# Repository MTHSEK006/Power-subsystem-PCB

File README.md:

**EEE3088 Power Sub-system Project 
MTHSEK006 & MKFMOR011**

**Description**  

This project involves the design and development of the micro-mouse power sub-system. The power sub-system is used to power the entire micro-mouse. This project is designed and developed in Kicad. Production files are jlcpcb compatible because project PCB is developed by JLCPCB. There are eight requirements in total. These requirements will be equally divided between MTHSEK006 and MFKMOR011. MTHSEK006 requirements designs can be found under pearl_pcb_design branch and MFKMOR011 requirements design can be found under morena_pcb_design branch. MTHSEK006 requirements include: 
* The power sub-system should operate 4 motors.
* The power sub-system should have a battery monitoring module.
* The power sub-system should provide 2x external load switching.
* The power sub-system should have a ON/OFF switch.
  
MFKMORO11 requirements include: 
* The power sub-system battery should be charged.
* The power sub-system should have two charging modes.
* The power sub-system should be integrated with a USB-C port.
* The power sub-system should have a 3V3 and 5V output channel.
At the end of the project, the power sub-system should be able to integrate with other components of the micro-mouse which include the motherboard, processor, sensing unit and the microcontroller.

**Structure**  

* PCB_v2.1: This includes the final PCB design. Contains Kicad files. 
* PCB_v2: This is the intial PCB design. Contains Kicad files.
* Documents: This includes footprints, symbol libraries, datasheets. 
* Production: Contains the gerber, clp and bom files.

**Usage**

  * The files needed to produce this PCB are found under Production. This folder can be downloaded and directly used for production.  
  * The final PCB design can be viewed by downloading PCB_v2.1 and opening the project in Kicad. 
 
**Contact** 

* Pearl Mothiba- MTHSEK006@myuct.ac.za
* Morena Mofokeng- MKFMOR011@myuct.ac.za
  
**Authors and Acknowledgement**

Authors 
* Pearl Mothiba
* Morena Mofokeng

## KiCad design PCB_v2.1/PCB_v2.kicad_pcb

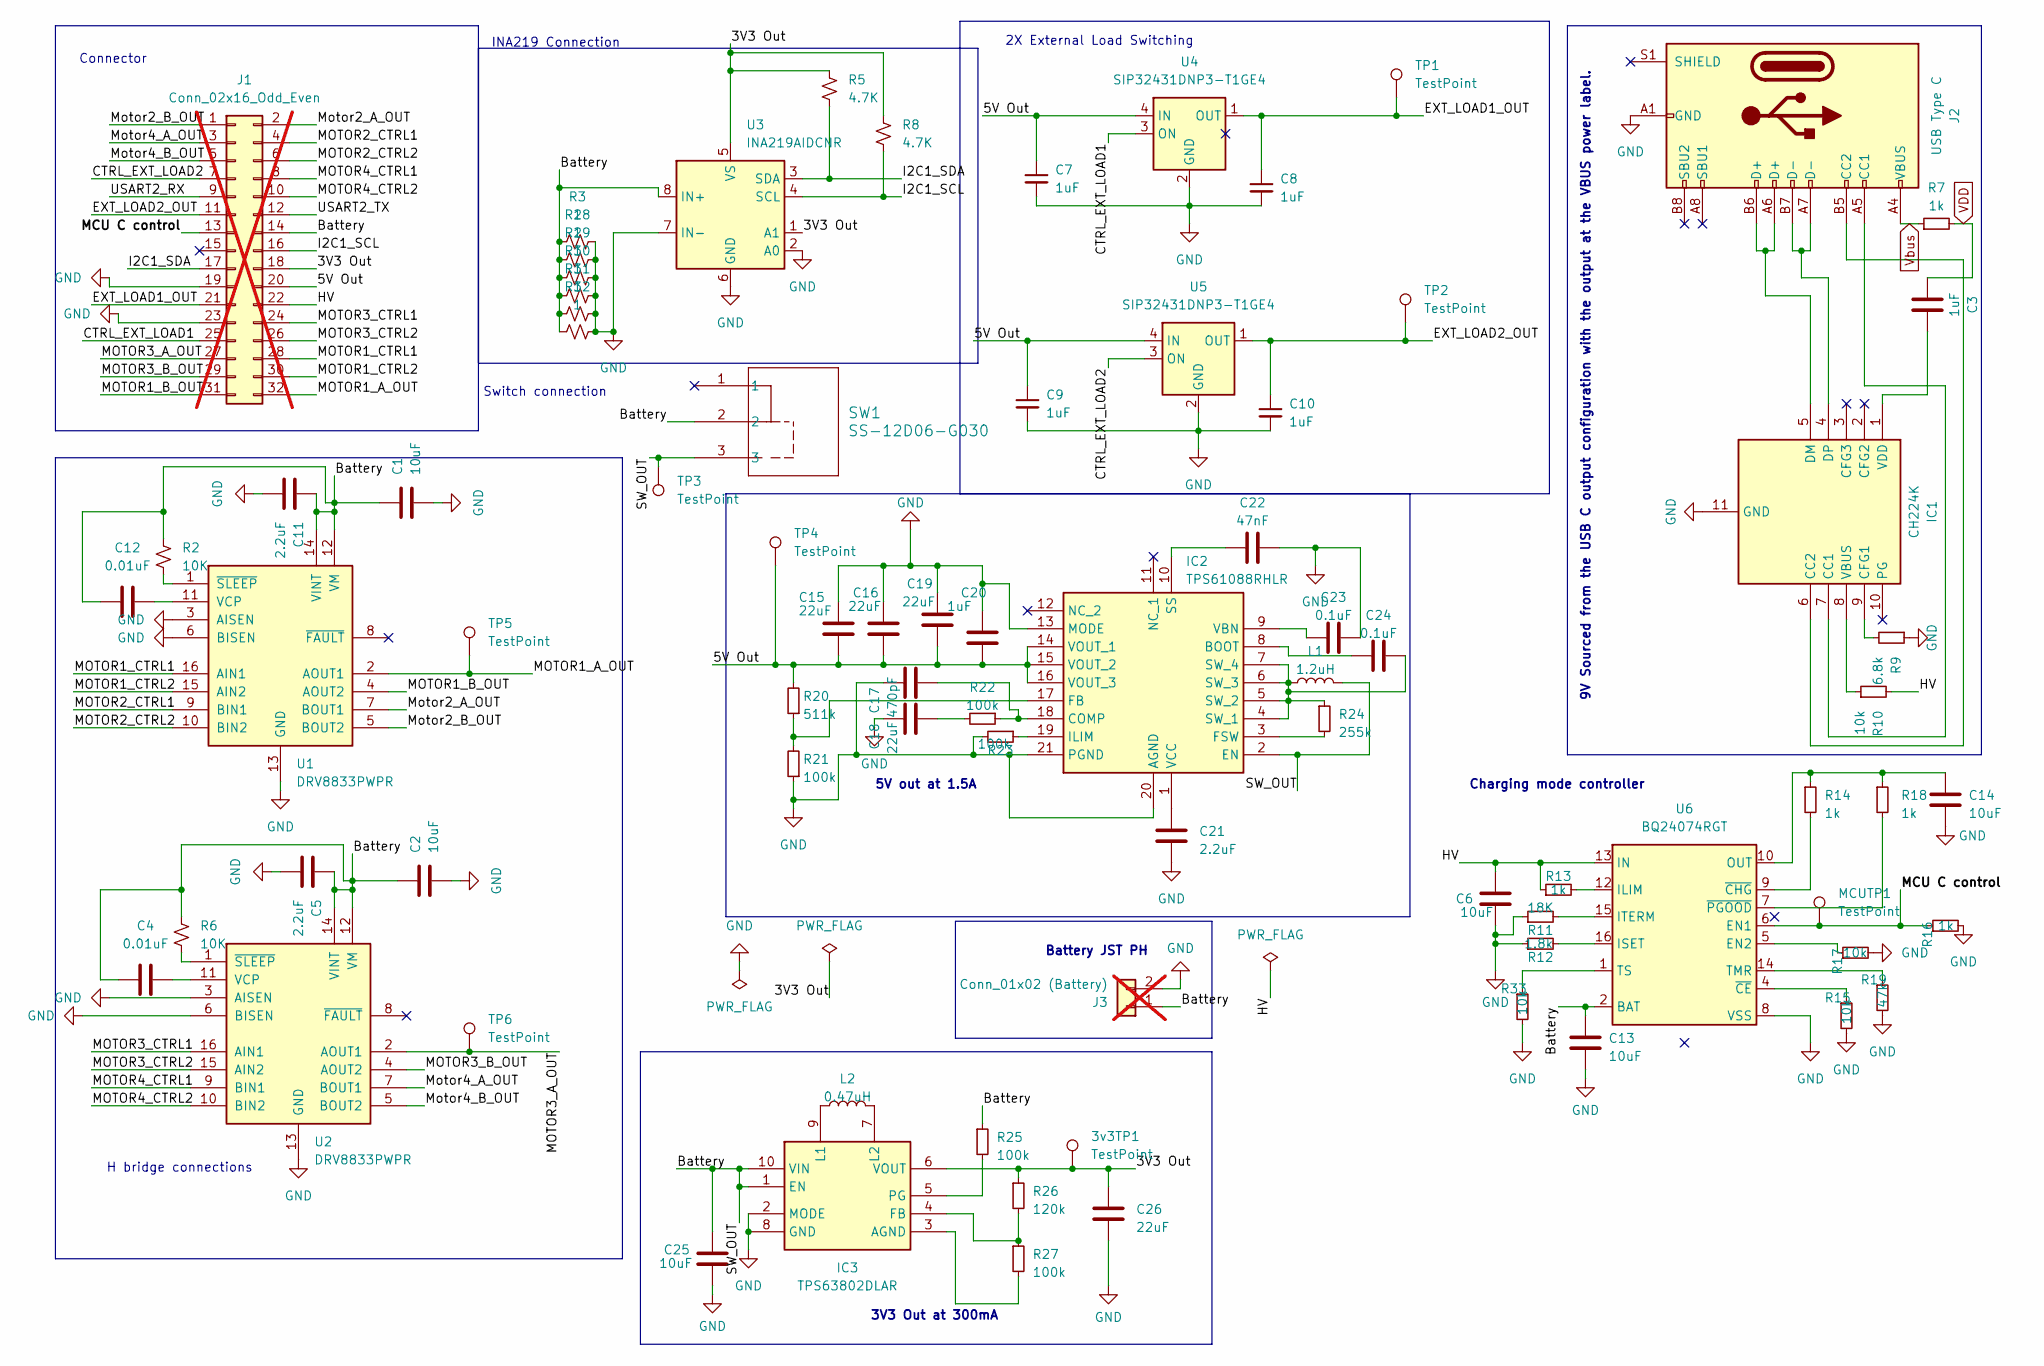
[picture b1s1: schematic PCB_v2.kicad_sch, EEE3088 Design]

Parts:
3v3TP1: TestPoint; TestPoint_Pad_1.0x1.0mm
C1, C2, C6, C13, C14, C25: 10uF; C_1206_3216Metric_Pad1.33x1.80mm_HandSolder; LCSC C13585
C3, C7, C8, C9, C10: 1uF; C_1206_3216Metric_Pad1.33x1.80mm_HandSolder; LCSC C1848
C4, C12: 0.01uF; C_0805_2012Metric_Pad1.18x1.45mm_HandSolder; LCSC C1710
C5, C11, C21: 2.2uF; C_0603_1608Metric_Pad1.08x0.95mm_HandSolder; LCSC C23630
C15, C16, C18, C19, C26: 22uF; C_1206_3216Metric_Pad1.33x1.80mm_HandSolder; LCSC C12891
C17: 470pF; C_0603_1608Metric_Pad1.08x0.95mm_HandSolder; LCSC C1620
C20: 1uF; C_1206_3216Metric_Pad1.33x1.80mm_HandSolder; LCSC C12891
C22: 47nF; C_0603_1608Metric_Pad1.08x0.95mm_HandSolder; LCSC C1622
C23, C24: 0.1uF; C_0402_1005Metric_Pad0.74x0.62mm_HandSolder; LCSC C1525
IC1: CH224K; SOP100P600X180-11N; Manufacturer_Part_Number CH224K; LCSC C970725
IC2: TPS61088RHLR; RHL(R-PVQFN-N20)_1; Manufacturer_Part_Number TPS61088RHLR; Mouser Part Number 595-TPS61088RHLR
IC3: TPS63802DLAR; Manufacturer_Part_Number TPS63802DLAR; Mouser Part Number 595-TPS63802DLAR
J1: Conn_02x16_Odd_Even; PinHeader_2x16_P2.54mm_Vertical; not fitted
J2: USB Type C; SHOUHAN_TYPE-C_16PIN_2MD__073_; LCSC C393939
J3: Conn_01x02 (Battery); SHDRRA2W50P0X200_1X2_590X760X480P; LCSC C173752; not fitted
L1: 1.2uH; L_0603_1608Metric_Pad1.05x0.95mm_HandSolder; LCSC C78176
L2: 0.47uH; L_0603_1608Metric_Pad1.05x0.95mm_HandSolder; LCSC C21307
MCUTP1: TestPoint; TestPoint_THTPad_1.0x1.0mm_Drill0.5mm
R2, R6: 10K; R_0805_2012Metric_Pad1.20x1.40mm_HandSolder; LCSC C17414
R3, R28, R29, R30, R31, R32: 1; R_1206_3216Metric_Pad1.30x1.75mm_HandSolder; LCSC C17928
R5, R8: 4.7K; R_1206_3216Metric_Pad1.30x1.75mm_HandSolder; LCSC C17936
R7, R13, R14, R16, R18: 1k; R_1206_3216Metric_Pad1.30x1.75mm_HandSolder; LCSC C4410
R9: 6.8k; R_0805_2012Metric_Pad1.20x1.40mm_HandSolder; LCSC C17772
R10, R15, R17, R33: 10k; R_0805_2012Metric_Pad1.20x1.40mm_HandSolder; LCSC C17414
R11: 18K; R_0603_1608Metric_Pad0.98x0.95mm_HandSolder; LCSC C25810
R12: 1.8k; R_0603_1608Metric_Pad0.98x0.95mm_HandSolder; LCSC C4177
R19: 47k; R_0805_2012Metric_Pad1.20x1.40mm_HandSolder; LCSC C17713
R20: 511k; R_0603_1608Metric_Pad0.98x0.95mm_HandSolder; LCSC C2930114
R21, R22, R23, R25, R27: 100k; R_0402_1005Metric_Pad0.72x0.64mm_HandSolder; LCSC C25741
R24: 255k; R_0402_1005Metric_Pad0.72x0.64mm_HandSolder; LCSC C226702
R26: 120k; R_0603_1608Metric_Pad0.98x0.95mm_HandSolder; LCSC C25808
SW1: SS-12D06-G030; SS-12D06_GSW; LCSC C17179519
TP1, TP2, TP3, TP4, TP5, TP6: TestPoint; TestPoint_Pad_1.0x1.0mm
U1, U2: DRV8833PWPR; HTSSOP-16-1EP_4.4x5mm_P0.65mm_EP3.4x5mm_Mask2.46x2.31mm; LCSC C50506
U3: INA219AIDCNR; SOT65P280X145-8N; LCSC C87469
U4, U5: SIP32431DNP3-T1GE4; SON50P120X160X60-5N; LCSC C727398
U6: BQ24074RGT; QFN50P300X300X100-17N-D; LCSC C54313

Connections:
/3V3 Out: 3v3TP1.1, C26.1, IC3.6 (VOUT), J1.18, R5.1, R8.1, R26.1, U3.1 (A1), U3.5 (VS)
/5V Out: C7.1, C9.1, C15.2, C16.2, C19.2, C20.2, IC2.14 (VOUT_1), IC2.15 (VOUT_2), IC2.16 (VOUT_3), J1.20, R20.2, TP4.1, U4.4 (IN), U5.4 (IN)
/Battery: C1.1, C2.1, C4.1, C5.1, C11.1, C12.1, C13.2, C25.1, IC2.2 (EN), IC3.1 (EN), IC3.10 (VIN), J1.14, J3.1, L1.2, R2.2, R3.1, R6.2, R25.1, R28.1, R29.1, R30.1, R31.1, R32.1, SW1.2, SW1.3, TP3.1, U1.12 (VM), U1.14 (VINT), U2.12 (VM), U2.14 (VINT), U3.8 (IN+), U6.2 (BAT)
/CTRL_EXT_LOAD1: J1.25, U4.3 (ON)
/CTRL_EXT_LOAD2: J1.7, U5.3 (ON)
/EXT_LOAD1_OUT: C8.1, J1.21, TP1.1, U4.1 (OUT)
/EXT_LOAD2_OUT: C10.1, J1.11, TP2.1, U5.1 (OUT)
/HV: C6.2, J1.22, R10.2, R13.1, U6.13 (IN)
/I2C1_SCL: J1.16, R8.2, U3.4 (SCL)
/I2C1_SDA: J1.17, R5.2, U3.3 (SDA)
/MCU C control: J1.13, MCUTP1.1, R16.1, U6.6 (EN1)
/MOTOR1_A_OUT: J1.32, TP5.1, U1.2 (AOUT1)
/MOTOR1_B_OUT: J1.31, U1.4 (AOUT2)
/MOTOR1_CTRL1: J1.28, U1.16 (AIN1)
/MOTOR1_CTRL2: J1.30, U1.15 (AIN2)
/MOTOR2_CTRL1: J1.4, U1.9 (BIN1)
/MOTOR2_CTRL2: J1.6, U1.10 (BIN2)
/MOTOR3_A_OUT: J1.27, TP6.1, U2.2 (AOUT1)
/MOTOR3_B_OUT: J1.29, U2.4 (AOUT2)
/MOTOR3_CTRL1: J1.24, U2.16 (AIN1)
/MOTOR3_CTRL2: J1.26, U2.15 (AIN2)
/MOTOR4_CTRL1: J1.8, U2.9 (BIN1)
/MOTOR4_CTRL2: J1.10, U2.10 (BIN2)
/Motor2_A_OUT: J1.2, U1.7 (BOUT1)
/Motor2_B_OUT: J1.1, U1.5 (BOUT2)
/Motor4_A_OUT: J1.3, U2.7 (BOUT1)
/Motor4_B_OUT: J1.5, U2.5 (BOUT2)
/USART2_RX: J1.9
/USART2_TX: J1.12
GND: C1.2, C2.2, C5.2, C6.1, C7.2, C8.2, C9.2, C10.2, C11.2, C13.1, C14.1, C15.1, C16.1, C17.1, C18.1, C19.1, C20.1, C21.1, C22.1, C23.1, C25.2, C26.2, IC1.11 (GND), IC2.13 (MODE), IC2.20 (AGND), IC2.21 (PGND), IC3.2 (MODE), IC3.8 (GND), J1.19, J1.23, J2.A1 (GND), J2.A12 (GND), J2.B1 (GND), J2.B12 (GND), J3.2, R3.2, R9.1, R11.1, R12.1, R15.2, R16.2, R17.2, R19.2, R21.1, R23.2, R28.2, R29.2, R30.2, R31.2, R32.2, R33.2, U1.3 (AISEN), U1.6 (BISEN), U1.13 (GND), U1.17 (GND), U2.3 (AISEN), U2.6 (BISEN), U2.13 (GND), U2.17 (GND), U3.2 (A0), U3.6 (GND), U3.7 (IN-), U4.2 (GND), U4.5 (GND), U5.2 (GND), U5.5 (GND), U6.8 (VSS)
unnamed: C14.2, R14.1, R18.1, U6.10 (OUT), U6.11 (OUT)
unnamed: C18.2, R22.2
unnamed: IC1.7 (CC1), J2.A5 (CC1)
unnamed: IC1.6 (CC2), J2.B5 (CC2)
unnamed: IC1.9 (CFG1), R9.2
unnamed: IC1.5 (DM), J2.A6 (D+), J2.B6 (D+)
unnamed: IC1.4 (DP), J2.A7 (D-), J2.B7 (D-)
unnamed: IC1.8 (VBUS), R10.1
unnamed: C3.2, IC1.1 (VDD)
unnamed: C24.2, IC2.8 (BOOT)
unnamed: C17.2, IC2.18 (COMP), R22.1
unnamed: IC2.17 (FB), R20.1, R21.2
unnamed: IC2.3 (FSW), R24.2
unnamed: IC2.19 (ILIM), R23.1
unnamed: C22.2, IC2.10 (SS)
unnamed: C24.1, IC2.4 (SW_1), IC2.5 (SW_2), IC2.6 (SW_3), IC2.7 (SW_4), L1.1, R24.1
unnamed: C23.2, IC2.9 (VBN)
unnamed: C21.2, IC2.1 (VCC)
unnamed: IC3.3 (AGND), R27.2
unnamed: IC3.4 (FB), R26.2, R27.1
unnamed: IC3.9 (L1), L2.1
unnamed: IC3.7 (L2), L2.2
unnamed: IC3.5 (PG), R25.2
unnamed: C12.2, U1.11 (VCP)
unnamed: R2.1, U1.1 (~SLEEP)
unnamed: C4.2, U2.11 (VCP)
unnamed: R6.1, U2.1 (~SLEEP)
unnamed: R17.1, U6.5 (EN2)
unnamed: R13.2, U6.12 (ILIM)
unnamed: R12.2, U6.16 (ISET)
unnamed: R11.2, U6.15 (ITERM)
unnamed: R19.1, U6.14 (TMR)
unnamed: R33.1, U6.1 (TS)
unnamed: R15.1, U6.4 (~CE)
unnamed: R14.2, U6.9 (~CHG)
unnamed: R18.2, U6.7 (~PGOOD)
VDD: C3.1, R7.2
Vbus: J2.A4 (VBUS), J2.A9 (VBUS), J2.B4 (VBUS), J2.B9 (VBUS), R7.1

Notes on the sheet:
Connector
2X External Load Switching
Switch connection
INA219 Connection
Charging mode controller
H bridge connections
9V Sourced from the USB C output configuration with the output at the VBUS power label.
Battery JST PH
3V3 Out at 300mA
5V out at 1.5A

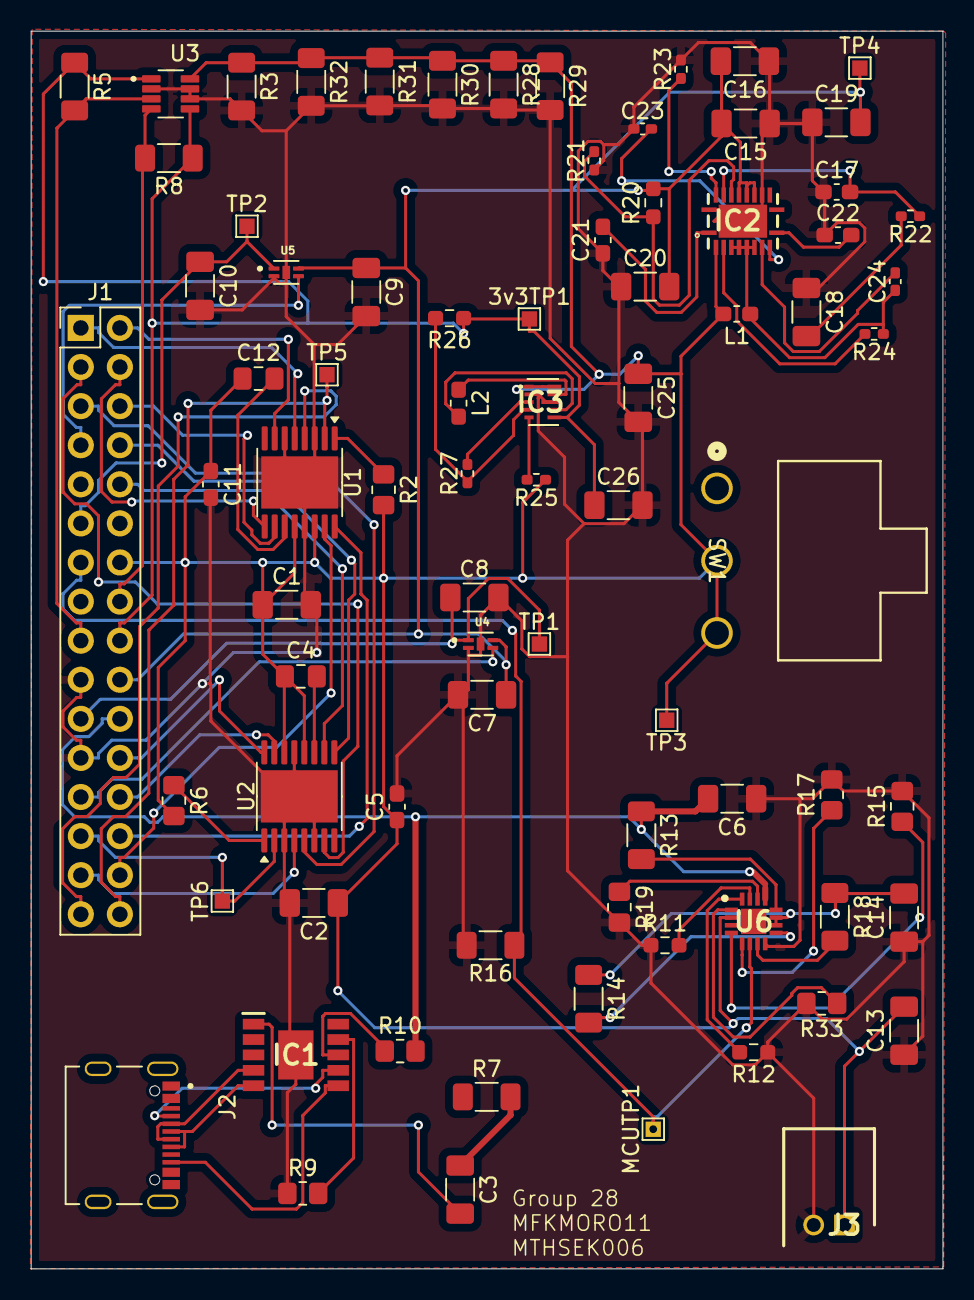
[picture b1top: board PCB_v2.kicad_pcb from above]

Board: 2 copper layers, 59.3 x 80.4 mm, 80 parts (0 on the bottom side), 65 nets.

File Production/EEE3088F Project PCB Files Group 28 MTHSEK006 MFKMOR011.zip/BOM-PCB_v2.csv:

Comment,Designator,Footprint,LCSC,Quantity
22uF,"C15,C16,C18,C19,C20,C26",C_1206_3216Metric_Pad1.33x1.80mm_HandSolder,C12891,6
10uF,"C1,C13,C14,C2,C25,C6",C_1206_3216Metric_Pad1.33x1.80mm_HandSolder,C13585,6
0.1uF,"C23,C24",C_0402_1005Metric_Pad0.74x0.62mm_HandSolder,C1525,2
470pF,C17,C_0603_1608Metric_Pad1.08x0.95mm_HandSolder,C1620,1
47nF,C22,C_0603_1608Metric_Pad1.08x0.95mm_HandSolder,C1622,1
0.01uF,"C12,C4",C_0805_2012Metric_Pad1.18x1.45mm_HandSolder,C1710,2
SS-12D06-G030,SW1,SS-12D06_GSW,C17179519,1
10k,"R10,R15,R17,R2,R33,R6",R_0805_2012Metric_Pad1.20x1.40mm_HandSolder,C17414,6
47k,R19,R_0805_2012Metric_Pad1.20x1.40mm_HandSolder,C17713,1
6.8k,R9,R_0805_2012Metric_Pad1.20x1.40mm_HandSolder,C17772,1
1,"R28,R29,R3,R30,R31,R32",R_1206_3216Metric_Pad1.30x1.75mm_HandSolder,C17928,6
4.7K,"R5,R8",R_1206_3216Metric_Pad1.30x1.75mm_HandSolder,C17936,2
1uF,"C10,C3,C7,C8,C9",C_1206_3216Metric_Pad1.33x1.80mm_HandSolder,C1848,5
0.47uH,L2,L_0603_1608Metric_Pad1.05x0.95mm_HandSolder,C21307,1
255k,R24,R_0402_1005Metric_Pad0.72x0.64mm_HandSolder,C226702,1
2.2uF,"C11,C21,C5",C_0603_1608Metric_Pad1.08x0.95mm_HandSolder,C23630,3
100k,"R21,R22,R23,R25,R27",R_0402_1005Metric_Pad0.72x0.64mm_HandSolder,C25741,5
120k,R26,R_0603_1608Metric_Pad0.98x0.95mm_HandSolder,C25808,1
18K,R11,R_0603_1608Metric_Pad0.98x0.95mm_HandSolder,C25810,1
TPS63802DLAR,IC3,TPS63802DLAR,C2845237,1
511k,R20,R_0603_1608Metric_Pad0.98x0.95mm_HandSolder,C2930114,1
USB Type C,J2,SHOUHAN_TYPE-C_16PIN_2MD__073_,C393939,1
1.8k,R12,R_0603_1608Metric_Pad0.98x0.95mm_HandSolder,C4177,1
1k,"R13,R14,R16,R18,R7",R_1206_3216Metric_Pad1.30x1.75mm_HandSolder,C4410,5
DRV8833PWPR,"U1,U2",HTSSOP-16-1EP_4.4x5mm_P0.65mm_EP3.4x5mm_Mask2.46x2.31mm,C50506,2
BQ24074RGT,U6,QFN50P300X300X100-17N-D,C54313,1
SIP32431DNP3-T1GE4,"U4,U5",SON50P120X160X60-5N,C727398,2
1.2uH,L1,L_0603_1608Metric_Pad1.05x0.95mm_HandSolder,C78176,1
TPS61088RHLR,IC2,RHL(R-PVQFN-N20)_1,C87357,1
INA219AIDCNR,U3,SOT65P280X145-8N,C87469,1
CH224K,IC1,SOP100P600X180-11N,C970725,1
TestPoint,TP6,TestPoint_Pad_1.0x1.0mm,,1
TestPoint,TP5,TestPoint_Pad_1.0x1.0mm,,1
TestPoint,TP2,TestPoint_Pad_1.0x1.0mm,,1
TestPoint,TP1,TestPoint_Pad_1.0x1.0mm,,1
TestPoint,TP3,TestPoint_Pad_1.0x1.0mm,,1
TestPoint,3v3TP1,TestPoint_Pad_1.0x1.0mm,,1
TestPoint,TP4,TestPoint_Pad_1.0x1.0mm,,1
TestPoint,MCUTP1,TestPoint_THTPad_1.0x1.0mm_Drill0.5mm,,1

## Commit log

2025-03-25 I replaced the PCB project that was in the folder initially and replaced it with the one I have been working on that is fully up to date.
2025-03-27 Merged with pearl_pcb_design
2025-03-27 Latest updates made with some footprints.
2025-03-27 Initial commit added
2025-04-24 Create PCB
2025-04-24 Add files via upload
    latest version of power sub-system upload
2025-04-24 EEE3088 Power sub-system
2025-04-24 libraries added
2025-04-24 production files
